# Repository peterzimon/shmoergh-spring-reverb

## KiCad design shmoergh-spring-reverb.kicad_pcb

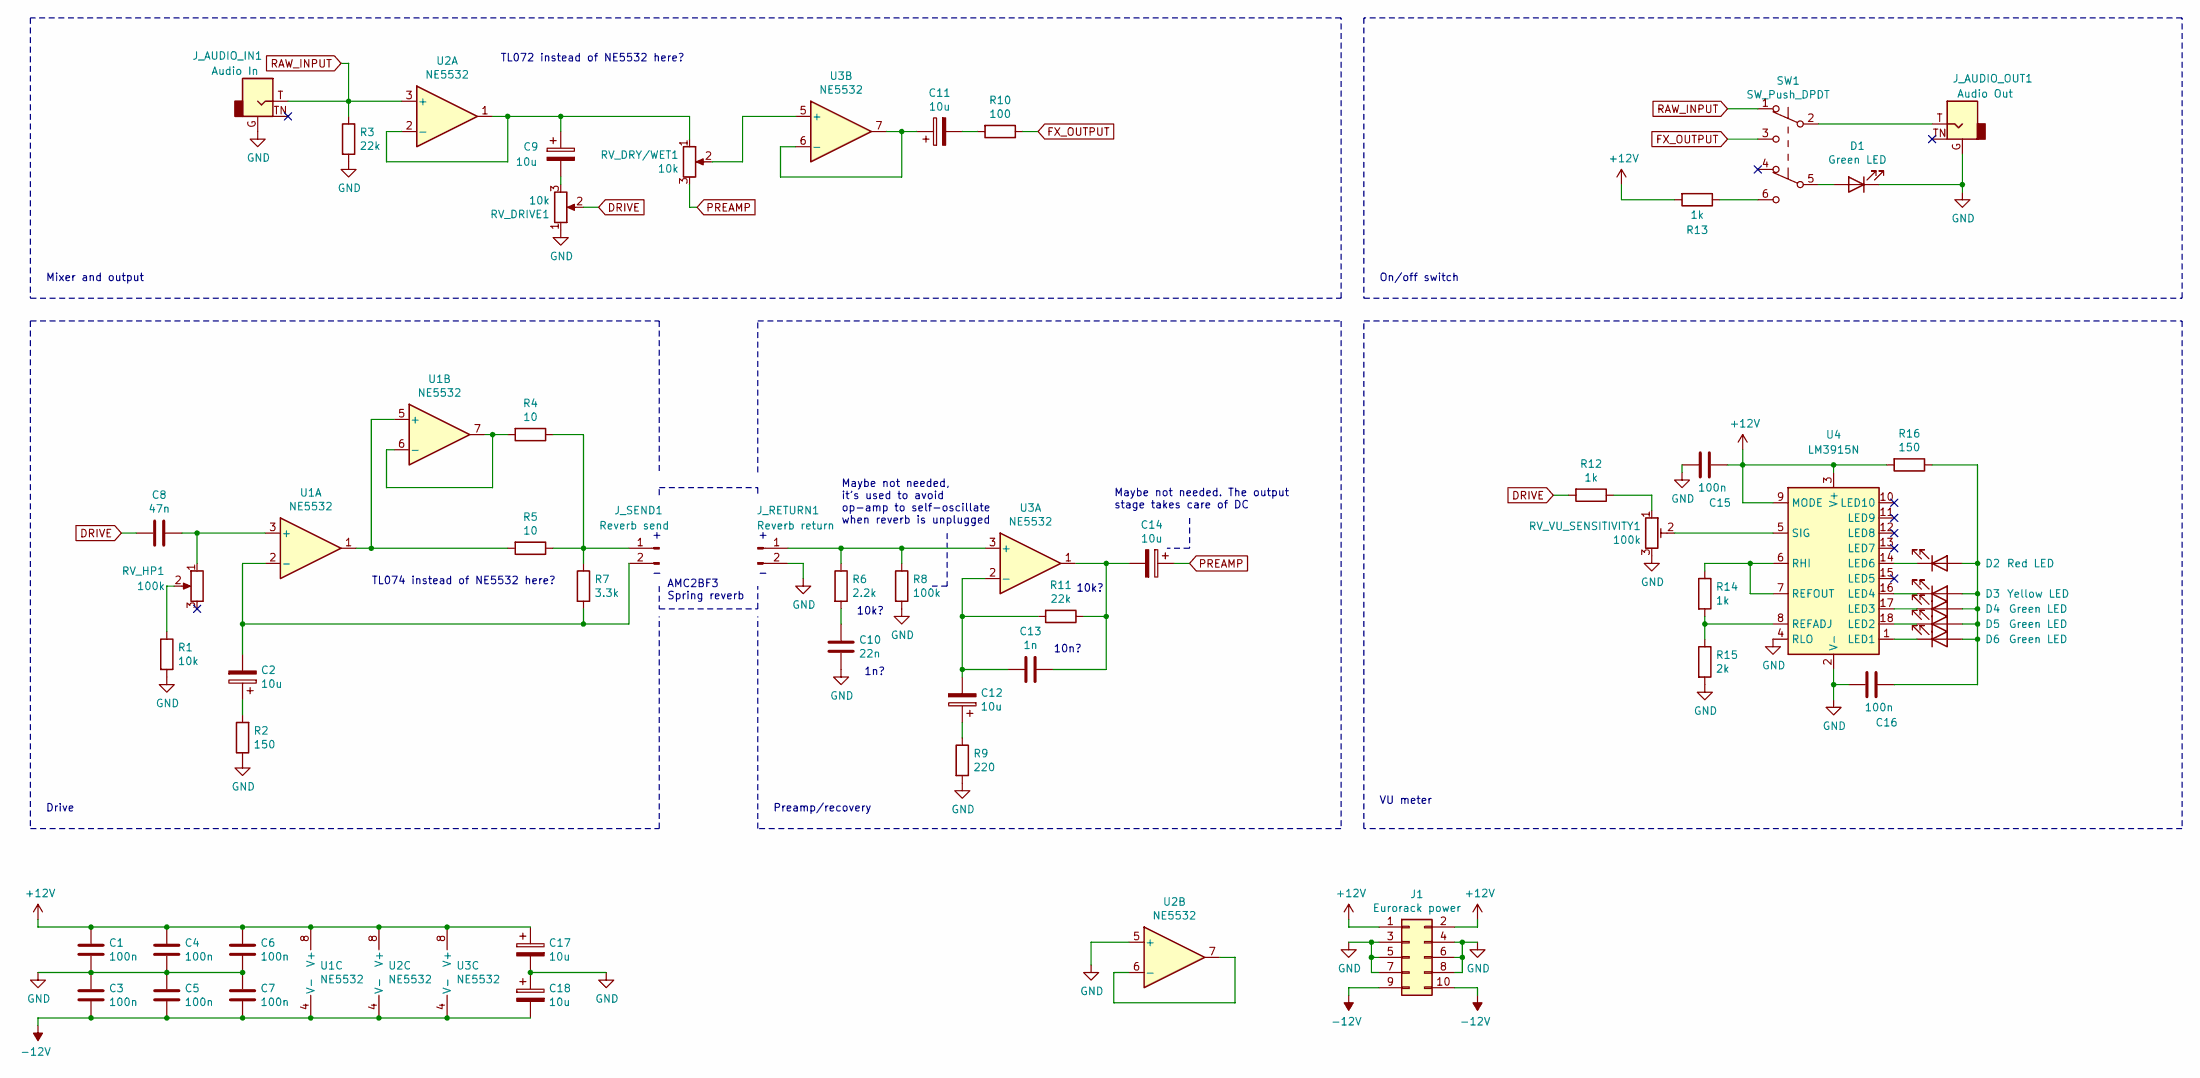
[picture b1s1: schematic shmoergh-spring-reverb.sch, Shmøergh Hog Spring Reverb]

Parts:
C1, C3, C4, C5, C6, C7, C15, C16: 100n; C_Disc_D5.0mm_W2.5mm_P2.50mm
C2, C9, C11, C12, C14, C17, C18: 10u; CP_Radial_D5.0mm_P2.50mm
C8: 47n; C_Disc_D5.0mm_W2.5mm_P2.50mm
C10: 22n; C_Disc_D5.0mm_W2.5mm_P2.50mm
C13: 1n; C_Disc_D5.0mm_W2.5mm_P2.50mm
D1, D4, D5, D6: Green LED; D_Axial-Vertical
D2: Red LED; D_Axial-Vertical
D3: Yellow LED; D_Axial-Vertical
J1: Eurorack power; Eurorack_Power_Supply
J_AUDIO_IN1: Audio In; Jack_3.5mm_Thonkiconn
J_AUDIO_OUT1: Audio Out; Jack_3.5mm_Thonkiconn
J_RETURN1: Reverb return; NSL25_01x02_Vertical
J_SEND1: Reverb send; NSL25_01x02_Vertical
R1: 10k; R_Axial_Vertical
R2, R16: 150; R_Axial_Vertical
R3, R11: 22k; R_Axial_Vertical
R4, R5: 10; R_Axial_Vertical
R6: 2.2k; R_Axial_Vertical
R7: 3.3k; R_Axial_Vertical
R8: 100k; R_Axial_Vertical
R9: 220; R_Axial_Vertical
R10: 100; R_Axial_Vertical
R12, R13, R14: 1k; R_Axial_Vertical
R15: 2k; R_Axial_Vertical
RV_DRIVE1: 10k; Potentiometer_Alpha_RD901F-40-00D_Single_Vertical
RV_DRY/WET1: 10k; Potentiometer_Alpha_RD901F-40-00D_Single_Vertical
RV_HP1: 100k; Potentiometer_Alpha_RD901F-40-00D_Single_Vertical
RV_VU_SENSITIVITY1: 100k; TrimPot_Vertical
SW1: SW_Push_DPDT; Switch_DPDT
U1, U2, U3: NE5532; DIP-8_W7.62mm
U4: LM3915N; DIP-18_W7.62mm

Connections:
+12V: C1.1, C4.1, C6.1, C15.1, C17.1, J1.1, J1.2, R13.2, R16.2, U1.8 (V+), U2.8 (V+), U3.8 (V+), U4.3 (V+), U4.9 (MODE)
-12V: C3.2, C5.2, C7.2, C18.2, J1.9, J1.10, U1.4 (V-), U2.4 (V-), U3.4 (V-)
DRIVE: C8.2, R12.2, RV_DRIVE1.2
FX_OUTPUT: R10.1, SW1.3 (C)
GND: C1.2, C3.1, C4.2, C5.1, C6.2, C7.1, C10.2, C15.2, C16.2, C17.2, C18.1, D1.1 (K), J1.3, J1.4, J1.5, J1.6, J1.7, J1.8, J_AUDIO_IN1.G, J_AUDIO_OUT1.G, J_RETURN1.2, R1.2, R2.1, R3.2, R8.2, R9.2, R15.2, RV_DRIVE1.1, RV_VU_SENSITIVITY1.3, U2.5 (+), U4.2 (V-), U4.4 (RLO)
unnamed: C2.1, R2.2
unnamed: C2.2, J_SEND1.2, R7.2, U1.2 (-)
unnamed: C8.1, RV_HP1.1, U1.3 (+)
unnamed: C9.1, RV_DRY/WET1.1, U2.1, U2.2 (-)
unnamed: C9.2, RV_DRIVE1.3
unnamed: C10.1, R6.2
unnamed: C11.1, U3.6 (-), U3.7
unnamed: C11.2, R10.2
unnamed: C12.1, R9.1
unnamed: C12.2, C13.2, R11.2, U3.2 (-)
unnamed: C13.1, C14.2, R11.1, U3.1
unnamed: C16.1, D2.2 (A), D3.2 (A), D4.2 (A), D5.2 (A), D6.2 (A), R16.1
unnamed: D1.2 (A), SW1.5 (B)
unnamed: D2.1 (K), U4.14 (LED6)
unnamed: D3.1 (K), U4.16 (LED4)
unnamed: D4.1 (K), U4.17 (LED3)
unnamed: D5.1 (K), U4.18 (LED2)
unnamed: D6.1 (K), U4.1 (LED1)
unnamed: J_AUDIO_OUT1.T, SW1.2 (B)
unnamed: J_RETURN1.1, R6.1, R8.1, U3.3 (+)
unnamed: J_SEND1.1, R4.1, R5.1, R7.1
unnamed: R1.1, RV_HP1.2
unnamed: R4.2, U1.6 (-), U1.7
unnamed: R5.2, U1.1, U1.5 (+)
unnamed: R12.1, RV_VU_SENSITIVITY1.1
unnamed: R13.1, SW1.6 (C)
unnamed: R14.1, U4.6 (RHI), U4.7 (REFOUT)
unnamed: R14.2, R15.1, U4.8 (REFADJ)
unnamed: RV_DRY/WET1.2, U3.5 (+)
unnamed: RV_VU_SENSITIVITY1.2, U4.5 (SIG)
unnamed: U2.6 (-), U2.7
PREAMP: C14.1, RV_DRY/WET1.3
RAW_INPUT: J_AUDIO_IN1.T, R3.1, SW1.1 (A), U2.3 (+)

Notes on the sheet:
TL074 instead of NE5532 here?
10k?
1n?
10n?
Maybe not needed, it’s used to avoid op-amp to self-oscillate when reverb is unplugged
AMC2BF3 Spring reverb
Mixer and output
Drive
Preamp/recovery
TL072 instead of NE5532 here?
Maybe not needed. The output stage takes care of DC
On/off switch
VU meter

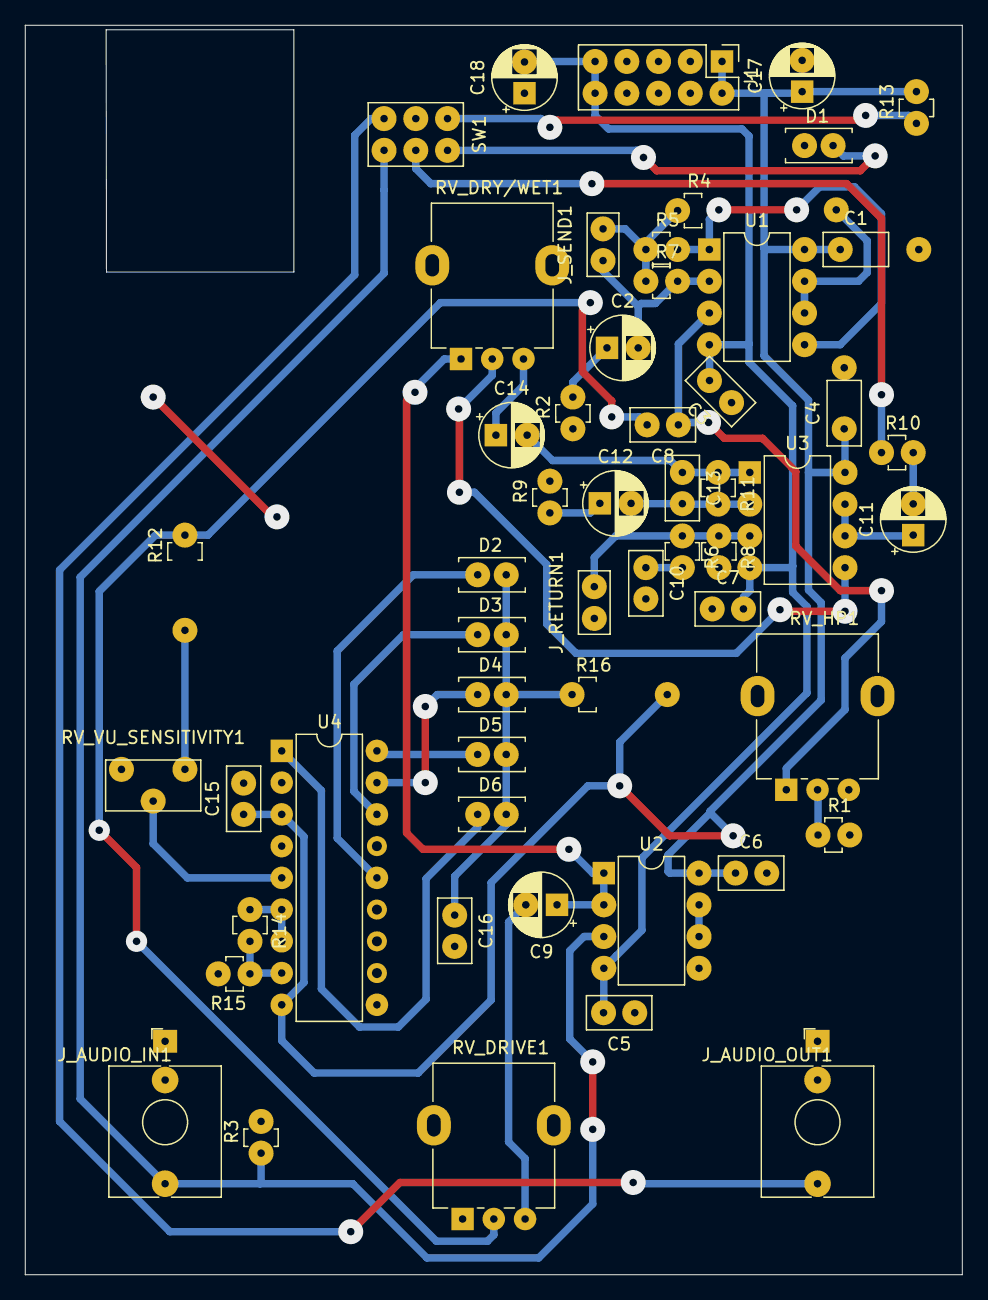
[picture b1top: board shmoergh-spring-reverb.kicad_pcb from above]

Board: 2 copper layers, 75.0 x 100.0 mm, 54 parts (0 on the bottom side), 38 nets.

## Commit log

2022-06-25 Added schematics
